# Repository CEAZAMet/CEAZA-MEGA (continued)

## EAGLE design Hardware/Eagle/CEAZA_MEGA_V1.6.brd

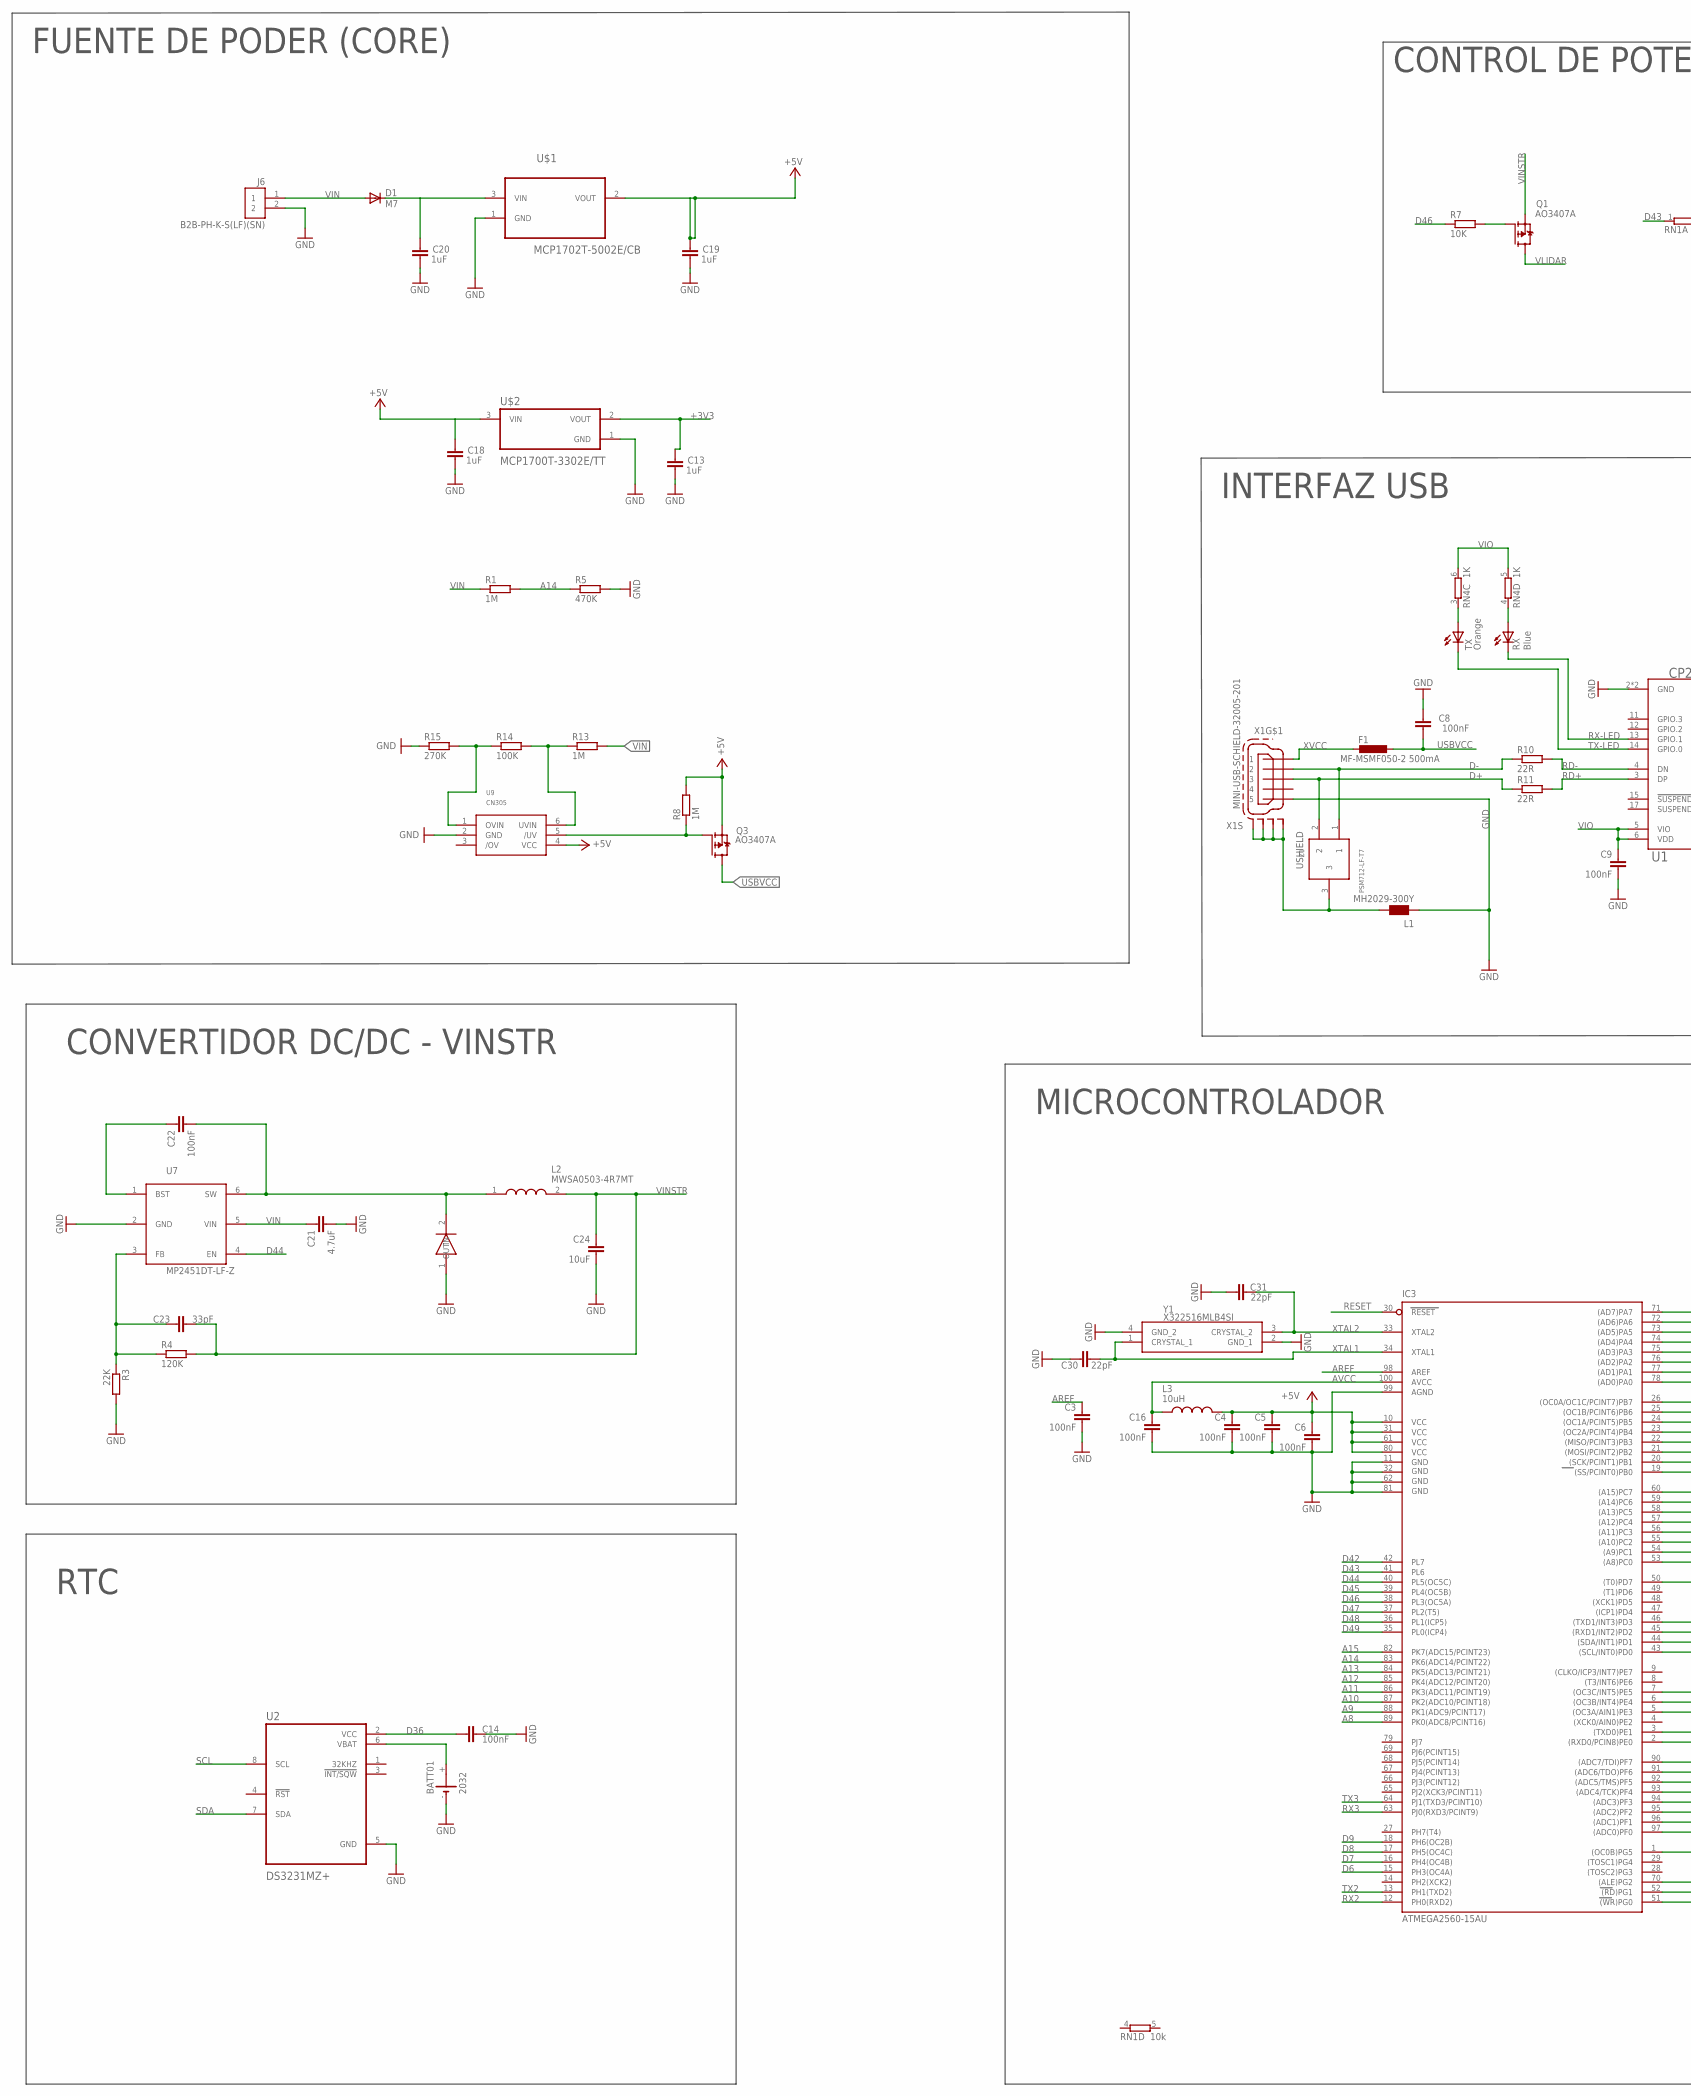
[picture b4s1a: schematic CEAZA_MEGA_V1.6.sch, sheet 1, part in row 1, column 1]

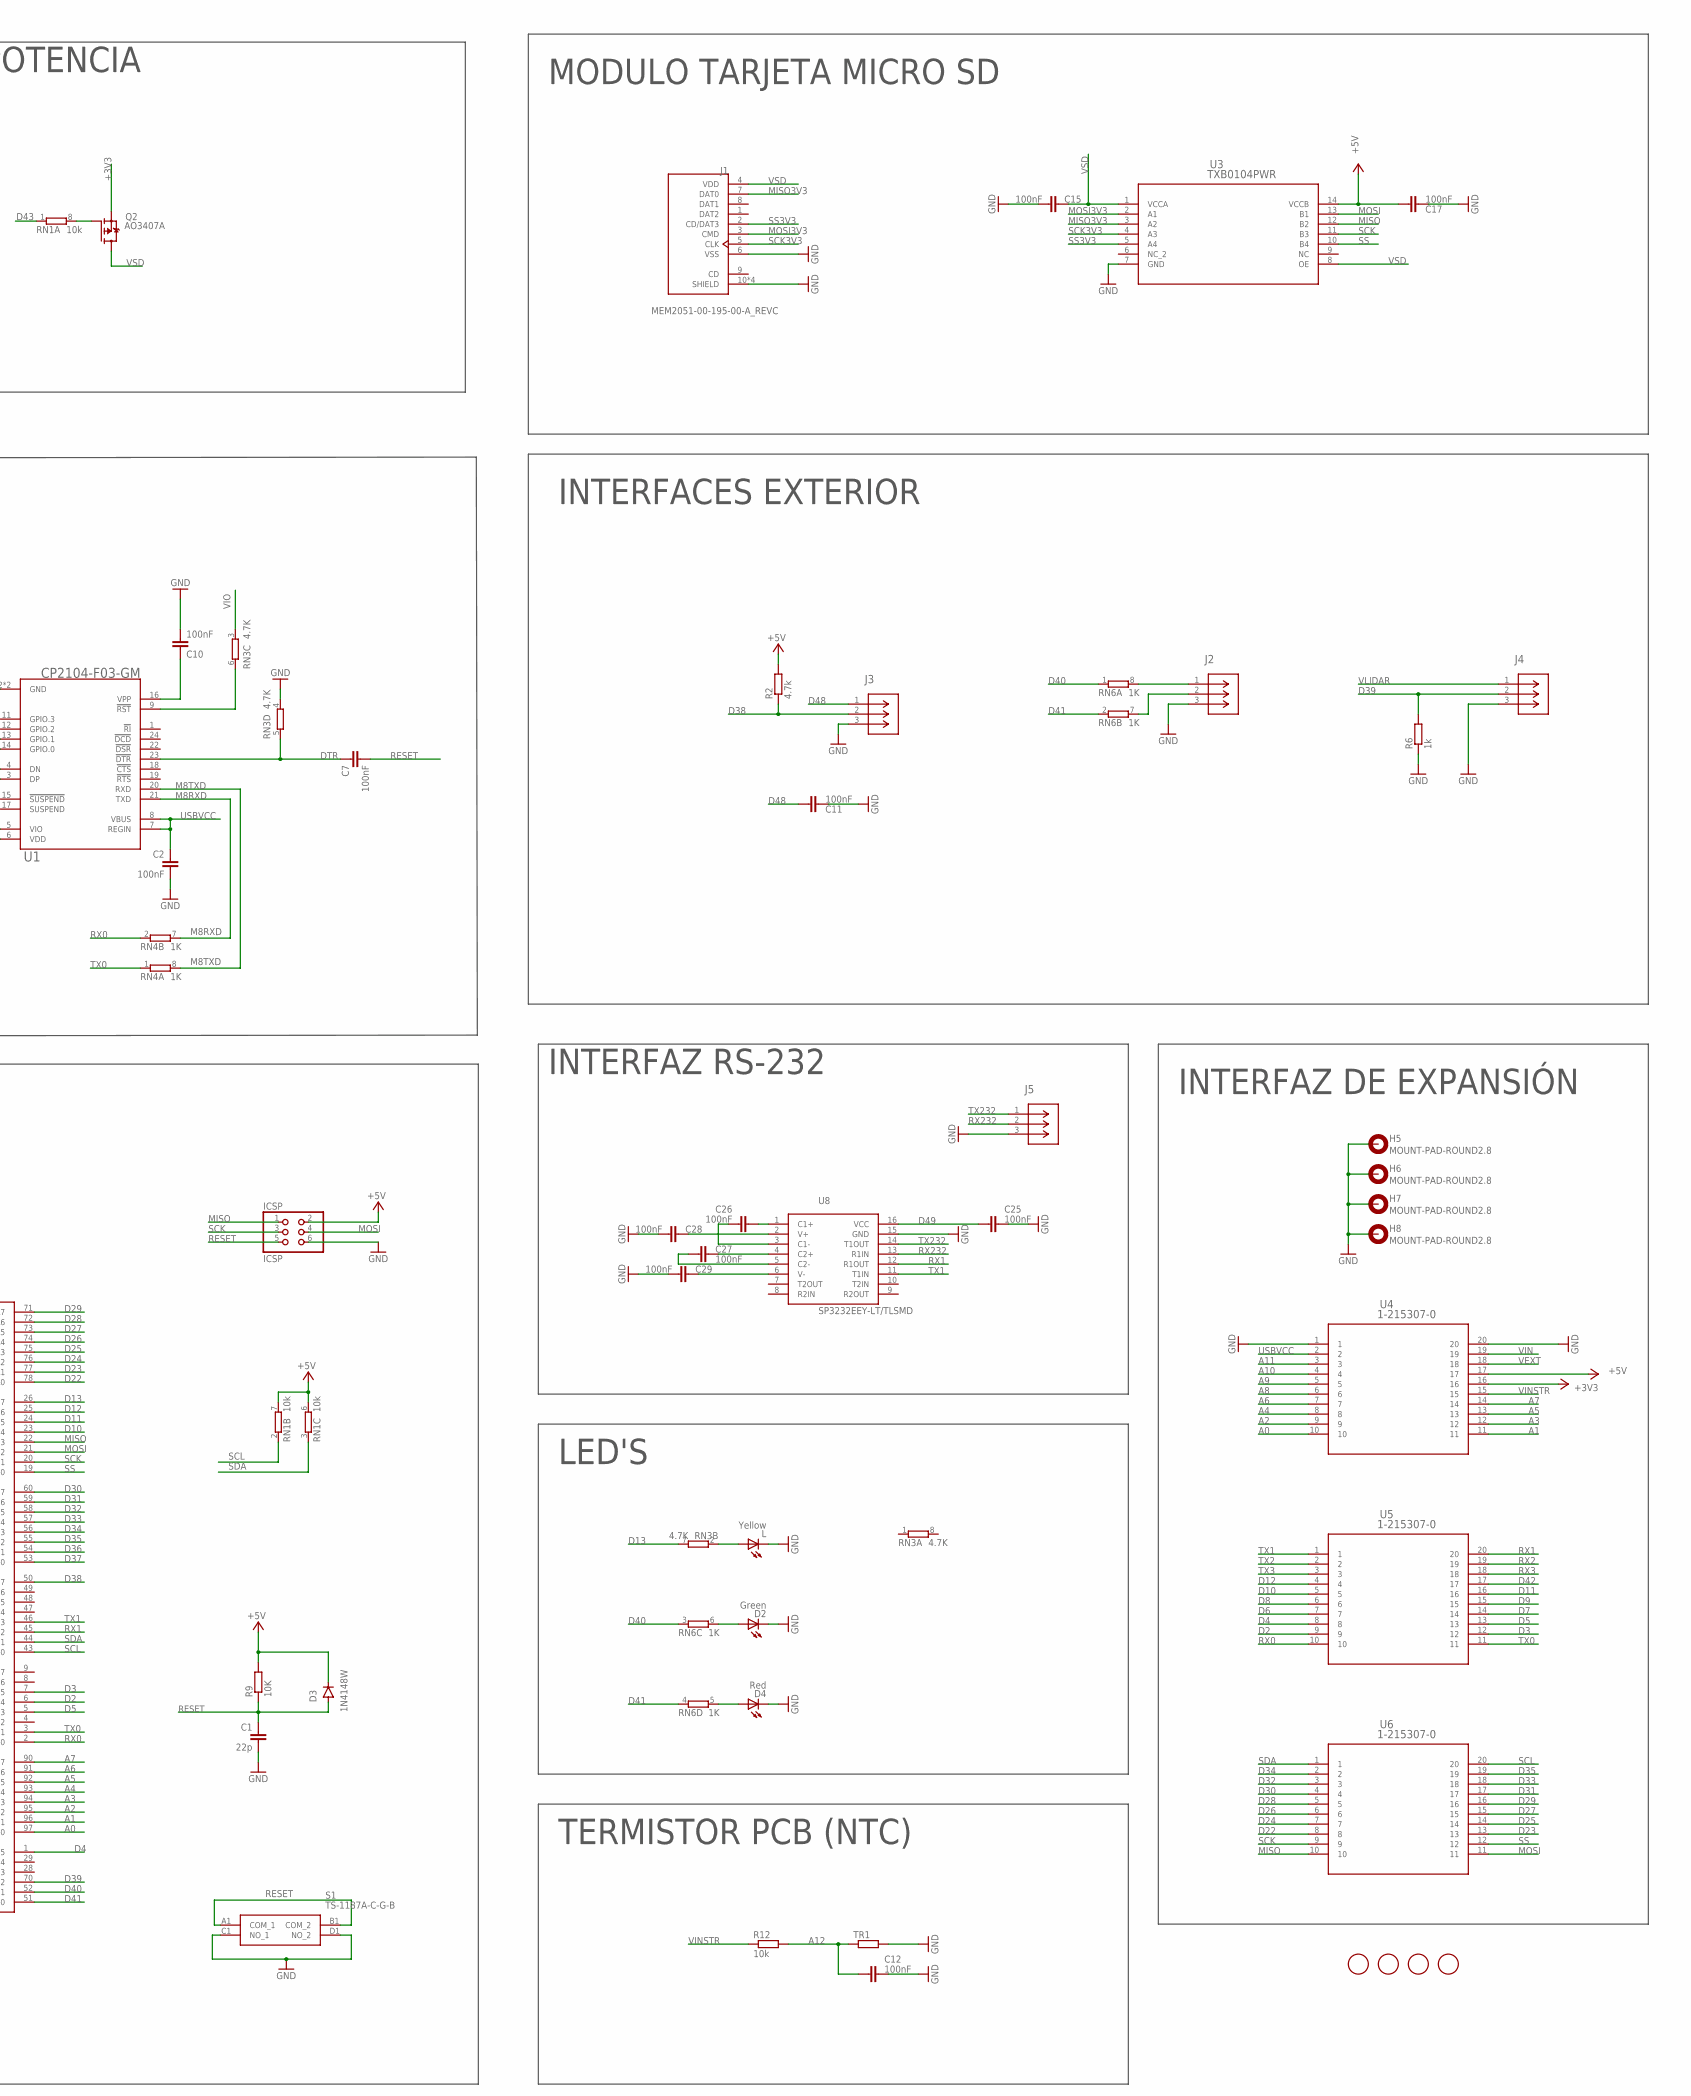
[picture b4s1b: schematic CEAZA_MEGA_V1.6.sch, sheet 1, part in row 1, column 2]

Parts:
BATT01: 2032; KZH20SMD
C1: 22p; C0603-ROUND
C2, C3, C4, C5, C6, C7, C8, C9, C10, C11, C12, C14, C15, C16, C17, C22, C25, C26, C27, C28, C29: 100nF; C0603-ROUND
C13, C18, C19, C20: 1uF; C0603-ROUND
C21: 4.7uF; C0603-ROUND
C23: 33pF; C0603-ROUND
C24: 10uF; C0603-ROUND
C30, C31: 22pF; C0603-ROUND
D1: M7; SMB
D2: Green; CHIPLED_0805
D3: 1N4148W; SOD-123_MINI-SMA
D4: Red; CHIPLED_0805
F1: MF-MSMF050-2 500mA; L1812
FD1, FD2, FD3, FD4: FIDUCIALMOUNT; FIDUCIA-MOUNT
H5, H6, H7, H8: MOUNT-PAD-ROUND2.8; 2,8-PAD
IC3: ATMEGA2560-15AU; TQFP100
ICSP: ICSP; 2X03
J1: MEM2051-00-195-00-A_REVC; GCT_MEM2051-00-195-00-A_REVC
J2, J3, J4, J5: B3B-PH-K-S(LF)(SN); CONN_B3B-PH-K-S(LF)(SN)_JST
J6: B2B-PH-K-S(LF)(SN); JST_B2B-PH-K-S(LF)(SN)
L: Yellow; CHIPLED_0805
L1: MH2029-300Y; 0805
L2: MWSA0503-4R7MT; MWSA0503
L3: 10uH; INDC1608X90N
Q1, Q2, Q3: AO3407A; SOT95P280X125-3N
R1, R8, R13: 1M; R0603
R2: 4.7k; R0603
R3: 22K; R0603
R4: 120K; R0603
R5: 470K; R0603
R6: 1k; R0603
R7, R9: 10K; R0603
R10, R11: 22R; R0603
R12: 10k; R0603
R14: 100K; R0603
R15: 270K; R0603
RN1: 10k; CAY16
RN3: 4.7K; CAY16
RN4: 1K; CAY16
RN6: 1K; 0603-ARV
RX: Blue; CHIPLED_0805
S1: TS-1187A-C-G-B; TS1187ACGB
TR1: R-EU_R0603; R0603
TX: Orange; CHIPLED_0805
U1: CP2104-F03-GM; QFN50P400X400X80-25N
U2: DS3231MZ+; SOIC127P600X175-8N
U3: TXB0104PWR; PW14
U4, U5, U6: 1-215307-0
U7: MP2451DT-LF-Z; SOT95P275X110-6N
U8: SP3232EEY-LT/TLSMD; SOP65P640X120-16N
U9: CN305; SOT23-6
U$1: MCP1702T-5002E/CB; SOT95P255X145-3N
U$2: MCP1700T-3302E/TT; SOT95P237X112-3N
U$3: SMA-SS34
X1: MINI-USB-SCHIELD-32005-201; 32005-201
Y1: X322516MLB4SI
Z1: PSM712-LF-T7; SOT23

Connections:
+3V3: C13.2, Q2.2 (S), U4.16, U$2.2 (VOUT)
+5V: C4.1, C5.1, C6.1, C17.2, C18.2, C19.2, D3.C, IC3.10 (VCC), IC3.31 (VCC1), IC3.61 (VCC2), IC3.80 (VCC3), ICSP.2, L3.2, Q3.2 (S), R2.2, R8.2, R9.2, RN1.6 (2), RN1.7 (2), U3.14 (VCCB), U4.17, U9.4 (VCC), U$1.2 (VOUT), U$2.3 (VIN)
A0: IC3.97 ((ADC0)PF0), U4.10
A1: IC3.96 ((ADC1)PF1), U4.11
A2: IC3.95 ((ADC2)PF2), U4.9
A3: IC3.94 ((ADC3)PF3), U4.12
A4: IC3.93 ((ADC4/TCK)PF4), U4.8
A5: IC3.92 ((ADC5/TMS)PF5), U4.13
A6: IC3.91 ((ADC6/TDO)PF6), U4.7
A7: IC3.90 ((ADC7/TDI)PF7), U4.14
A8: IC3.89 (PK0(ADC8/PCINT16)), U4.6
A9: IC3.88 (PK1(ADC9/PCINT17)), U4.5
A10: IC3.87 (PK2(ADC10/PCINT18)), U4.4
A11: IC3.86 (PK3(ADC11/PCINT19)), U4.3
A12: C12.1, IC3.85 (PK4(ADC12/PCINT20)), R12.2, TR1.1
A13: IC3.84 (PK5(ADC13/PCINT21))
A14: IC3.83 (PK6(ADC14/PCINT22)), R1.2, R5.1
A15: IC3.82 (PK7(ADC15/PCINT23))
AREF: C3.1, IC3.98 (AREF)
AVCC: C16.1, IC3.100 (AVCC), L3.1
D2: IC3.6 ((OC3B/INT4)PE4), U5.9
D3: IC3.7 ((OC3C/INT5)PE5), U5.12
D4: IC3.1 ((OC0B)PG5), U5.8
D5: IC3.5 ((OC3A/AIN1)PE3), U5.13
D6: IC3.15 (PH3(OC4A)), U5.7
D7: IC3.16 (PH4(OC4B)), U5.14
D8: IC3.17 (PH5(OC4C)), U5.6
D9: IC3.18 (PH6(OC2B)), U5.15
D10: IC3.23 ((OC2A/PCINT4)PB4), U5.5
D11: IC3.24 ((OC1A/PCINT5)PB5), U5.16
D12: IC3.25 ((OC1B/PCINT6)PB6), U5.4
D13: IC3.26 ((OC0A/OC1C/PCINT7)PB7), RN3.7 (2)
D22: IC3.78 ((AD0)PA0), U6.8
D23: IC3.77 ((AD1)PA1), U6.13
D24: IC3.76 ((AD2)PA2), U6.7
D25: IC3.75 ((AD3)PA3), U6.14
D26: IC3.74 ((AD4)PA4), U6.6
D27: IC3.73 ((AD5)PA5), U6.15
D28: IC3.72 ((AD6)PA6), U6.5
D29: IC3.71 ((AD7)PA7), U6.16
D30: IC3.60 ((A15)PC7), U6.4
D31: IC3.59 ((A14)PC6), U6.17
D32: IC3.58 ((A13)PC5), U6.3
D33: IC3.57 ((A12)PC4), U6.18
D34: IC3.56 ((A11)PC3), U6.2
D35: IC3.55 ((A10)PC2), U6.19
D36: C14.1, IC3.54 ((A9)PC1), U2.2 (VCC)
D37: IC3.53 ((A8)PC0)
D38: IC3.50 ((T0)PD7), J3.2, R2.1
D39: IC3.70 ((ALE)PG2), J4.2, R6.2
D40: IC3.52 ((RD)PG1), RN6.1, RN6.3 (1)
D41: IC3.51 ((WR)PG0), RN6.2 (1), RN6.4 (1)
D42: IC3.42 (PL7), U5.17
D43: IC3.41 (PL6), RN1.1
D44: IC3.40 (PL5(OC5C)), U7.4 (EN)
D45: IC3.39 (PL4(OC5B))
D46: IC3.38 (PL3(OC5A)), R7.1
D47: IC3.37 (PL2(T5))
D48: C11.2, IC3.36 (PL1(ICP5)), J3.1
D49: C25.1, IC3.35 (PL0(ICP4)), U8.16 (VCC)
D+: R11.1, X1.3, Z1.2
D-: R10.1, X1.2, Z1.1
DTR: C7.1, RN3.5 (2), U1.23 (!DTR)
GND: BATT01.-, C1.2, C2.2, C3.2, C4.2, C5.2, C6.2, C8.2, C9.2, C10.2, C11.1, C12.2, C13.1, C14.2, C15.2, C16.2, C17.1, C18.1, C19.1, C20.1, C21.2, C24.2, C25.2, C28.2, C29.2, C30.1, C31.2, D2.C, D4.C, H5.B2,8, H6.B2,8, H7.B2,8, H8.B2,8, IC3.11 (GND), IC3.32 (GND1), IC3.62 (GND2), IC3.81 (GND3), IC3.99 (AGND), ICSP.6, J1.6 (VSS), J1.10 (SHIELD), J1.11 (SHIELD), J1.12 (SHIELD), J1.13 (SHIELD), J2.3, J3.3, J4.3, J5.3, J6.2, L.C, L1.1, R3.2, R5.2, R6.1, R15.1, RN3.4 (1), S1.C1 (NO_1), S1.D1 (NO_2), TR1.2, U1.2 (GND), U1.25 (GND), U2.5 (GND), U3.7 (GND), U4.1, U4.20, U7.2 (GND), U8.15 (GND), U9.2 (GND), U$1.1 (GND), U$2.1 (GND), U$3.1 (IN), X1.5, Y1.2 (GND_1), Y1.4 (GND_2)
M8RXD: RN4.7 (2), U1.21 (TXD)
M8TXD: RN4.8 (2), U1.20 (RXD)
MISO: IC3.22 ((MISO/PCINT3)PB3), ICSP.1, U3.12 (B2), U6.10
MISO3V3: J1.7 (DAT0), U3.3 (A2)
MOSI: IC3.21 ((MOSI/PCINT2)PB2), ICSP.4, U3.13 (B1), U6.11
MOSI3V3: J1.3 (CMD), U3.2 (A1)
unnamed: C20.2, D1.C, U$1.3 (VIN)
unnamed: L.A, RN3.2 (1)
unnamed: D2.A, RN6.6 (2)
unnamed: RN3.6 (2), U1.9 (!RST!)
unnamed: C10.1, U1.16 (VPP)
unnamed: BATT01.+, U2.6 (VBAT)
unnamed: J2.1, RN6.8 (2)
unnamed: J2.2, RN6.7 (2)
unnamed: C22.2, L2.1, U7.6 (SW), U$3.2 (OUT)
unnamed: C22.1, U7.1 (BST)
unnamed: D4.A, RN6.5 (2)
unnamed: C23.1, R3.1, R4.1, U7.3 (FB)
unnamed: C26.1, U8.1 (C1+)
unnamed: C26.2, U8.3 (C1-)
unnamed: C27.1, U8.4 (C2+)
unnamed: C27.2, U8.5 (C2-)
unnamed: C28.1, U8.2 (V+)
unnamed: Q2.1 (G), RN1.8 (2)
unnamed: C29.1, U8.6 (V-)
unnamed: Q1.1 (G), R7.2
unnamed: Q3.1 (G), R8.1, U9.5 (/UV)
unnamed: RN4.3 (1), TX.A
unnamed: RN4.4 (1), RX.A
unnamed: R13.1, R14.2, U9.6 (UVIN)
unnamed: R14.1, R15.2, U9.1 (OVIN)
RD+: R11.2, U1.3 (DP)
RD-: R10.2, U1.4 (DN)
RESET: C1.1, C7.2, D3.A, IC3.30 (RESET), ICSP.5, R9.1, S1.A1 (COM_1), S1.B1 (COM_2)
RX0: IC3.2 ((RXD0/PCIN8)PE0), RN4.2 (1), U5.10
RX1: IC3.45 ((RXD1/INT2)PD2), U5.20, U8.12 (R1OUT)
RX2: IC3.12 (PH0(RXD2)), U5.19
RX3: IC3.63 (PJ0(RXD3/PCINT9)), U5.18
RX232: J5.2, U8.13 (R1IN)
RX-LED: RX.C, U1.13 (GPIO.1)
SCK: IC3.20 ((SCK/PCINT1)PB1), ICSP.3, U3.11 (B3), U6.9
SCK3V3: J1.5 (CLK), U3.4 (A3)
SCL: IC3.43 ((SCL/INT0)PD0), RN1.2 (1), U2.8 (SCL), U6.20
SDA: IC3.44 ((SDA/INT1)PD1), RN1.3 (1), U2.7 (SDA), U6.1
SS: IC3.19 ((SS/PCINT0)PB0), U3.10 (B4), U6.12
SS3V3: J1.2 (CD/DAT3), U3.5 (A4)
TX0: IC3.3 ((TXD0)PE1), RN4.1, U5.11
TX1: IC3.46 ((TXD1/INT3)PD3), U5.1, U8.11 (T1IN)
TX2: IC3.13 (PH1(TXD2)), U5.2
TX3: IC3.64 (PJ1(TXD3/PCINT10)), U5.3
TX232: J5.1, U8.14 (T1OUT)
TX-LED: TX.C, U1.14 (GPIO.0)
USBVCC: C2.1, C8.1, F1.1, Q3.3 (D), U1.7 (REGIN), U1.8 (VBUS), U4.2
USHIELD: L1.2, X1.M1 (S1), X1.M2 (S2), X1.M3 (S3), X1.M4 (S4), Z1.3
VEXT: U4.18
VIN: C21.1, D1.A, J6.1, R1.1, R13.2, U4.19, U7.5 (VIN)
VINSTR: C23.2, C24.1, L2.2, Q1.2 (S), R4.2, R12.1, U4.15
VIO: C9.1, RN3.3 (1), RN4.5 (2), RN4.6 (2), U1.5 (VIO), U1.6 (VDD)
VLIDAR: J4.1, Q1.3 (D)
VSD: C15.1, J1.4 (VDD), Q2.3 (D), U3.1 (VCCA), U3.8 (OE)
XTAL1: C30.2, IC3.34 (XTAL1), Y1.1 (CRYSTAL_1)
XTAL2: C31.1, IC3.33 (XTAL2), Y1.3 (CRYSTAL_2)
XVCC: F1.2, X1.1

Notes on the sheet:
MODULO TARJETA MICRO SD
INTERFAZ RS-232
CONTROL DE POTENCIA
RTC
FUENTE DE PODER (CORE)
CONVERTIDOR DC/DC - VINSTR
LED'S
INTERFACES EXTERIOR
MICROCONTROLADOR
INTERFAZ DE EXPANSIÓN
INTERFAZ USB
TERMISTOR PCB (NTC)

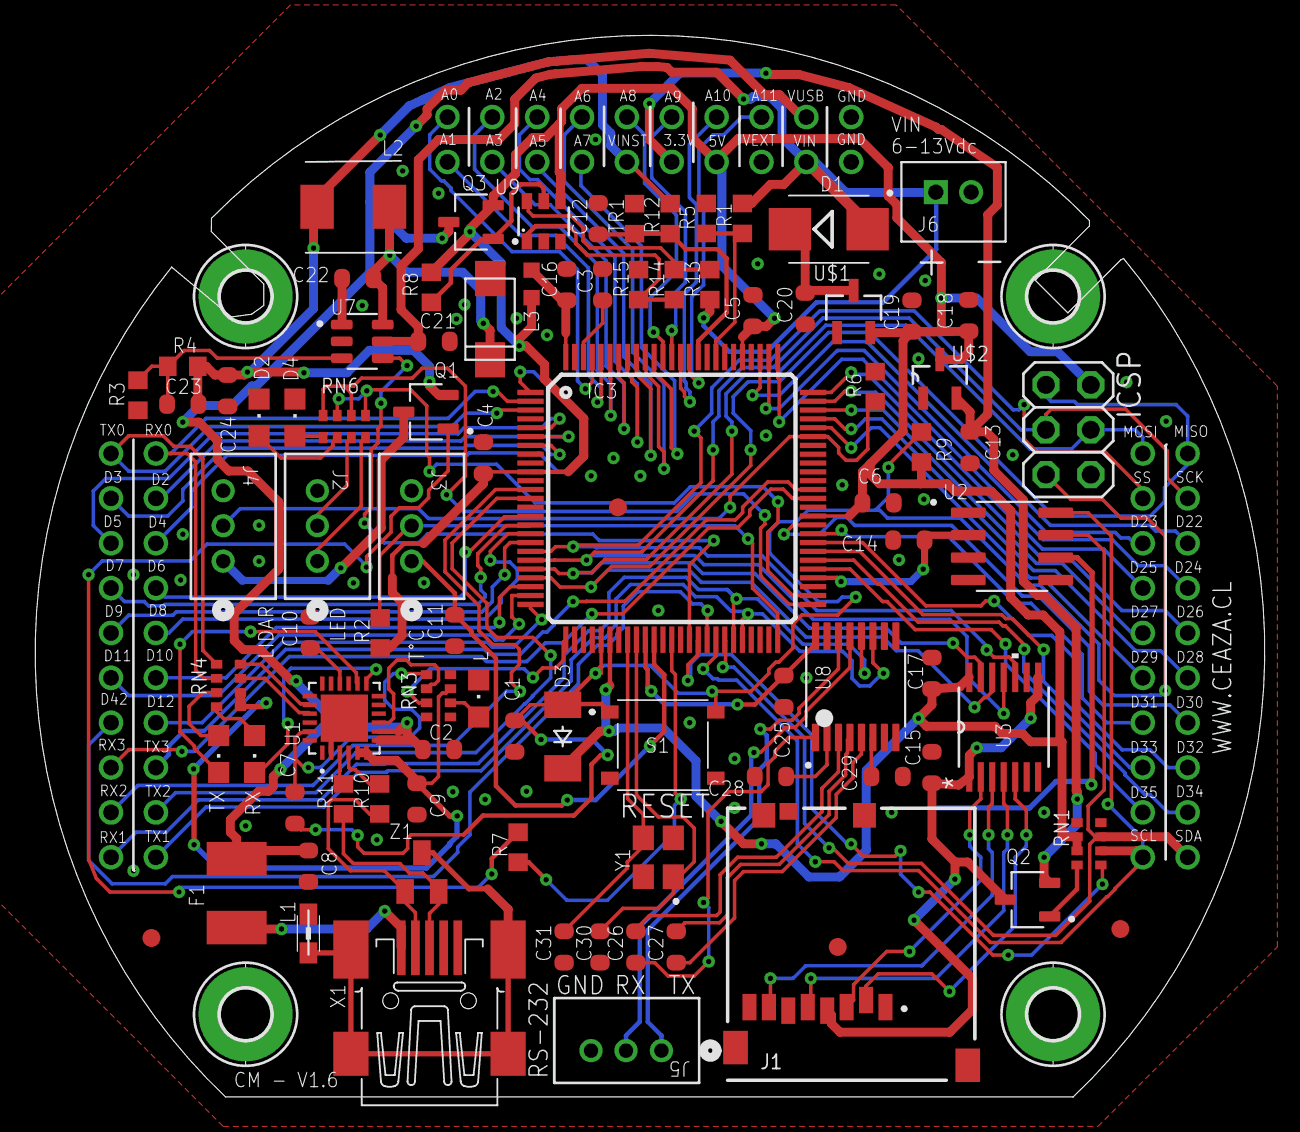
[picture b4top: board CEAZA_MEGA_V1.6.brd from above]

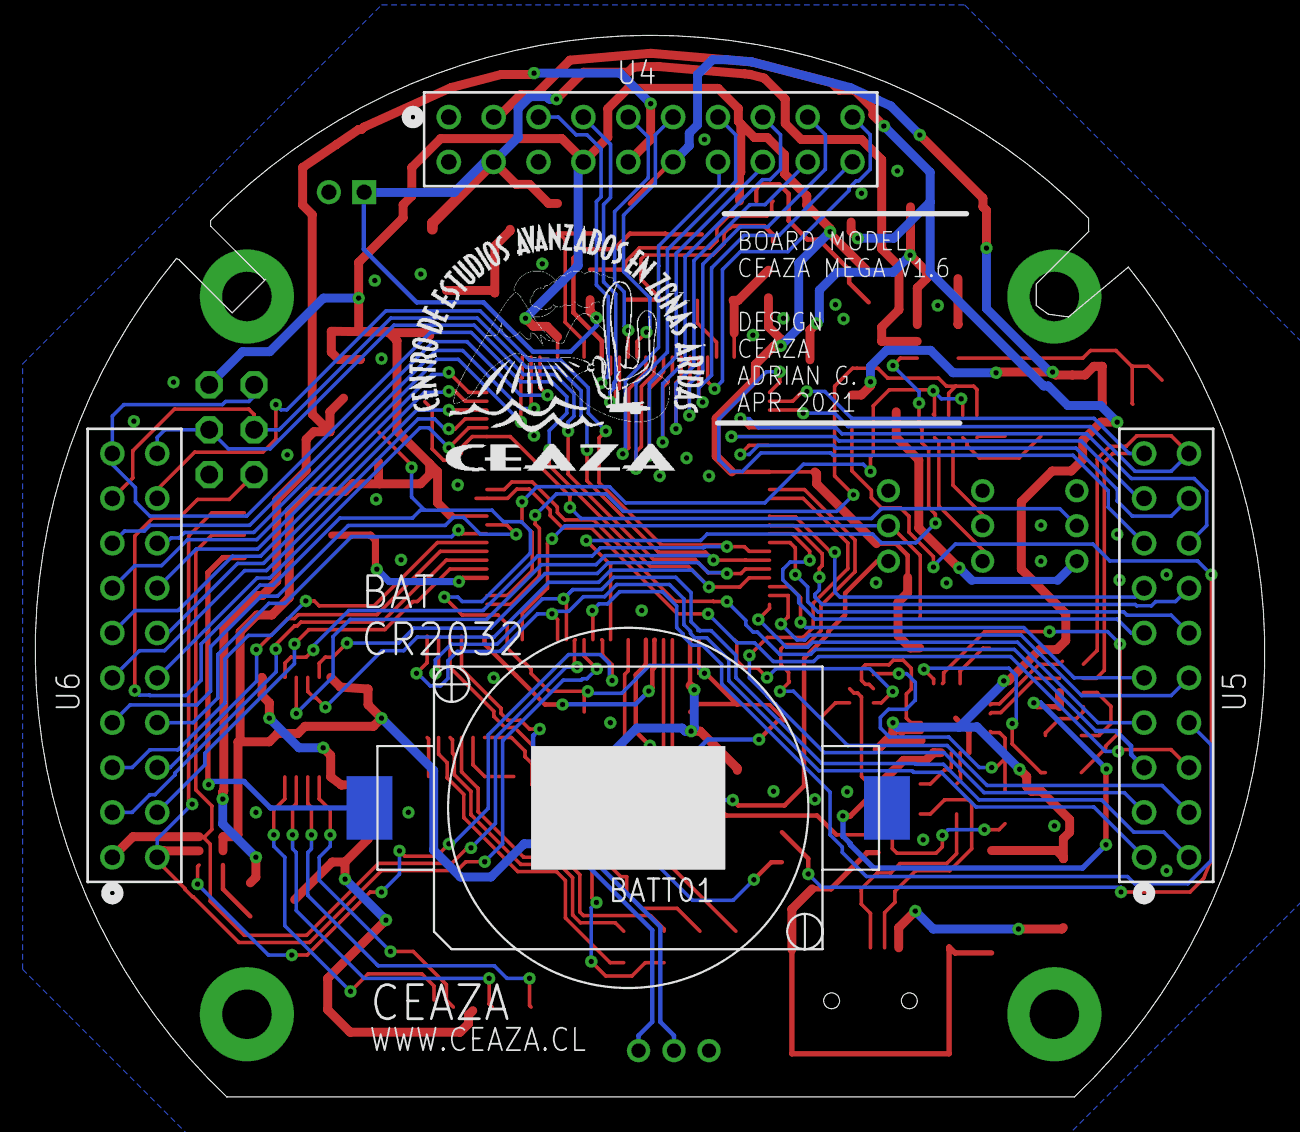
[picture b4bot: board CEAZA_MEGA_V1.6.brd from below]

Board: 2 copper layers, 69.6 x 60.1 mm, 98 parts (4 on the bottom side), 121 nets.

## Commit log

2022-07-01 Removed Redundant Copyright Notice
2022-07-01 Basic Formatting
2022-07-01 Added License Badge
2025-05-08 consolidar carpetas CEAZAMega
2025-05-08 cleanup
